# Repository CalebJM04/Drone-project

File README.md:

# Drone-project
Summer Drone project w/ Noah

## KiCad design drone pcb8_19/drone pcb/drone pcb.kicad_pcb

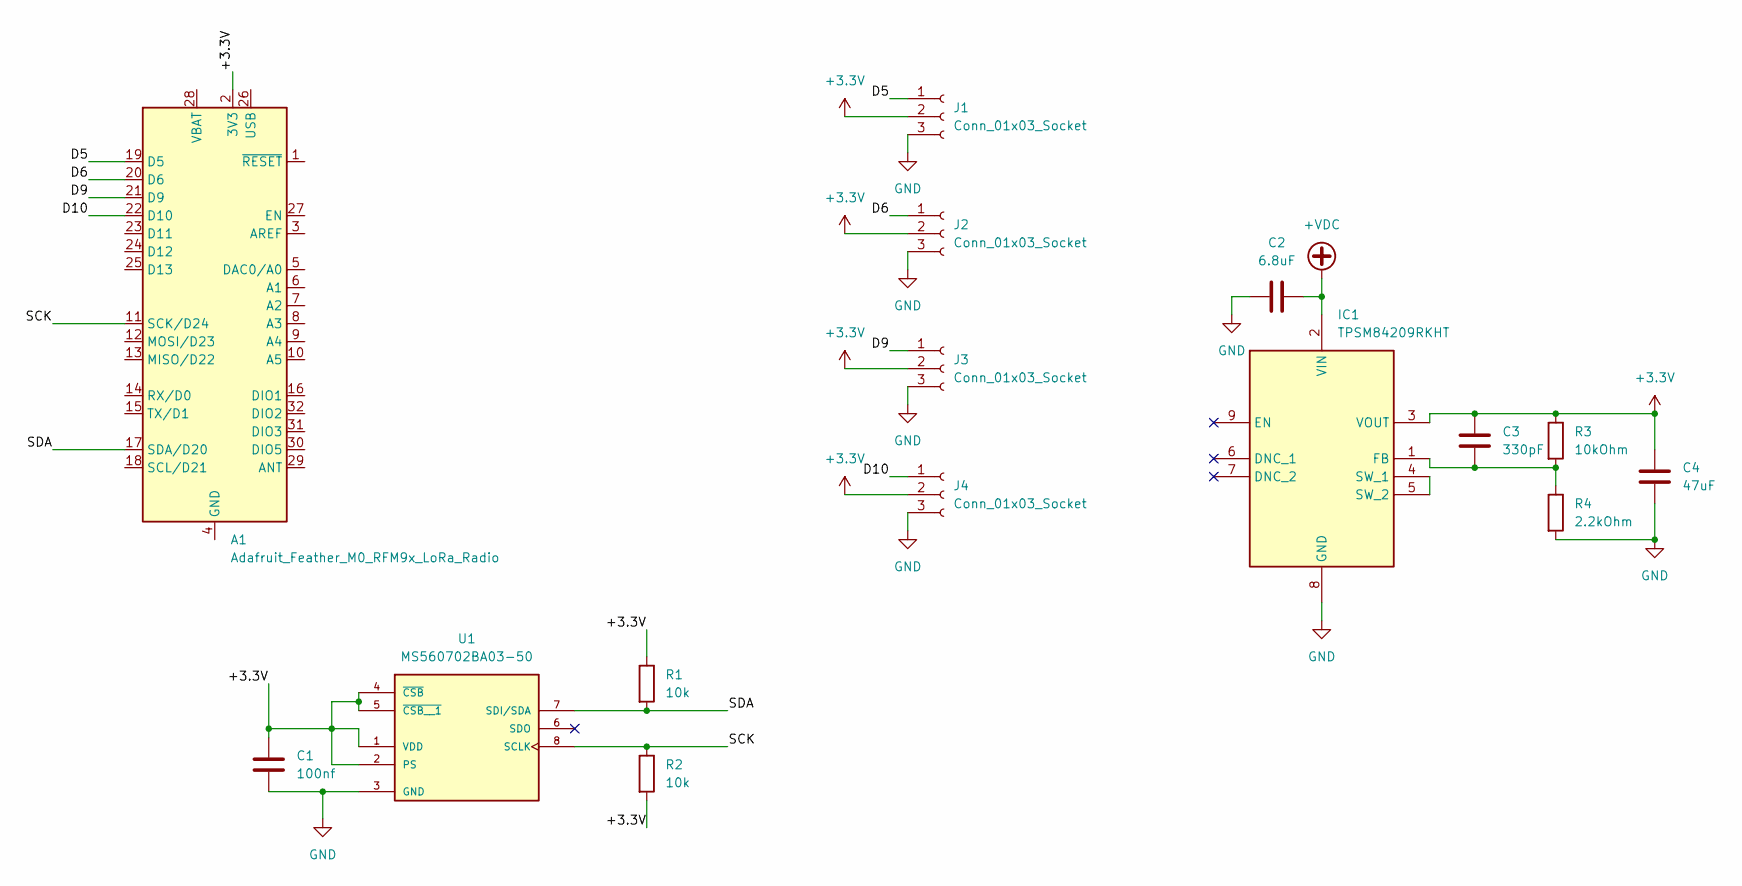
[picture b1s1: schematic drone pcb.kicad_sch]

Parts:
A1: Adafruit_Feather_M0_RFM9x_LoRa_Radio; Adafruit_Feather_M0_RFM
C1: 100nf; C_0603_1608Metric_Pad1.08x0.95mm_HandSolder
C2: 6.8uF; C_0603_1608Metric_Pad1.08x0.95mm_HandSolder
C3: 330pF; C_0603_1608Metric_Pad1.08x0.95mm_HandSolder
C4: 47uF; C_0603_1608Metric_Pad1.08x0.95mm_HandSolder
IC1: TPSM84209RKHT; Mouser Part Number 595-TPSM84209RKHT
J1, J2, J3, J4: Conn_01x03_Socket; PinSocket_1x03_P2.54mm_Vertical
R1, R2: 10k; R_0603_1608Metric_Pad0.98x0.95mm_HandSolder
R3: 10kOhm; R_0603_1608Metric_Pad0.98x0.95mm_HandSolder
R4: 2.2kOhm; R_0603_1608Metric_Pad0.98x0.95mm_HandSolder
U1: MS560702BA03-50; SON125P300X500X100-8N

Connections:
+3.3V: A1.2 (3V3), C1.1, C3.1, C4.1, IC1.3 (VOUT), J1.2, J2.2, J3.2, J4.2, R1.1, R2.2, R3.1, U1.1 (VDD), U1.2 (PS), U1.4 (~CSB), U1.5 (~CSB__1)
+VDC: C2.2, IC1.2 (VIN)
/D5: A1.19 (D5), J1.1
/D6: A1.20 (D6), J2.1
/D9: A1.21 (D9), J3.1
/D10: A1.22 (D10), J4.1
/SCK: A1.11 (SCK/D24), R2.1, U1.8 (SCLK)
/SDA: A1.17 (SDA/D20), R1.2, U1.7 (SDI/SDA)
GND: C1.2, C2.1, C4.2, IC1.8 (GND), J1.3, J2.3, J3.3, J4.3, R4.2, U1.3 (GND)
unnamed: C3.2, IC1.1 (FB), R3.2, R4.1
unnamed: IC1.4 (SW_1), IC1.5 (SW_2)

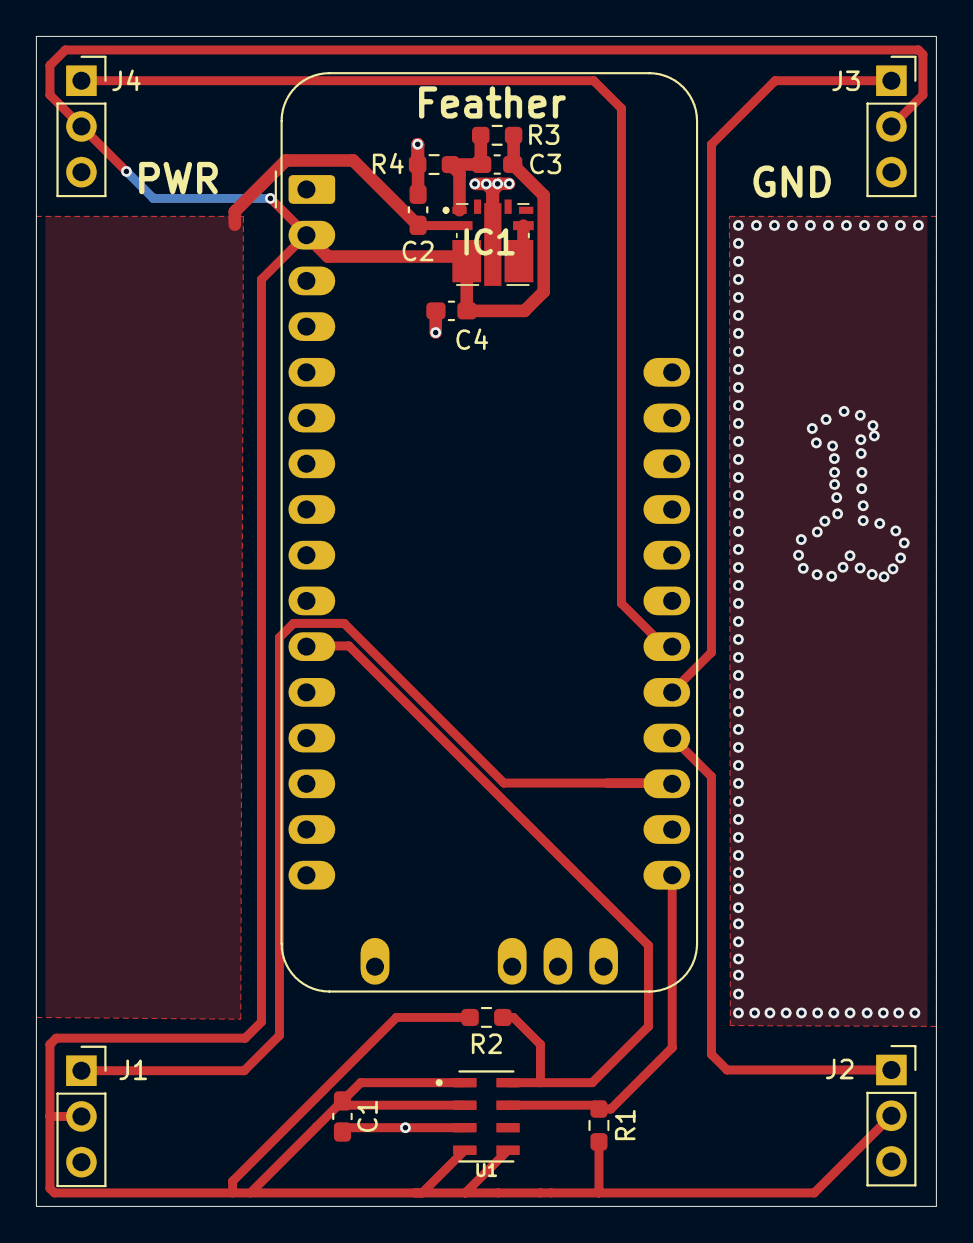
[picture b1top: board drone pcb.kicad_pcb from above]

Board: 2 copper layers, 50.0 x 65.0 mm, 15 parts (0 on the bottom side), 11 nets.

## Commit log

2025-08-21 KiCad PCB
2025-08-22 add feather power off battery
